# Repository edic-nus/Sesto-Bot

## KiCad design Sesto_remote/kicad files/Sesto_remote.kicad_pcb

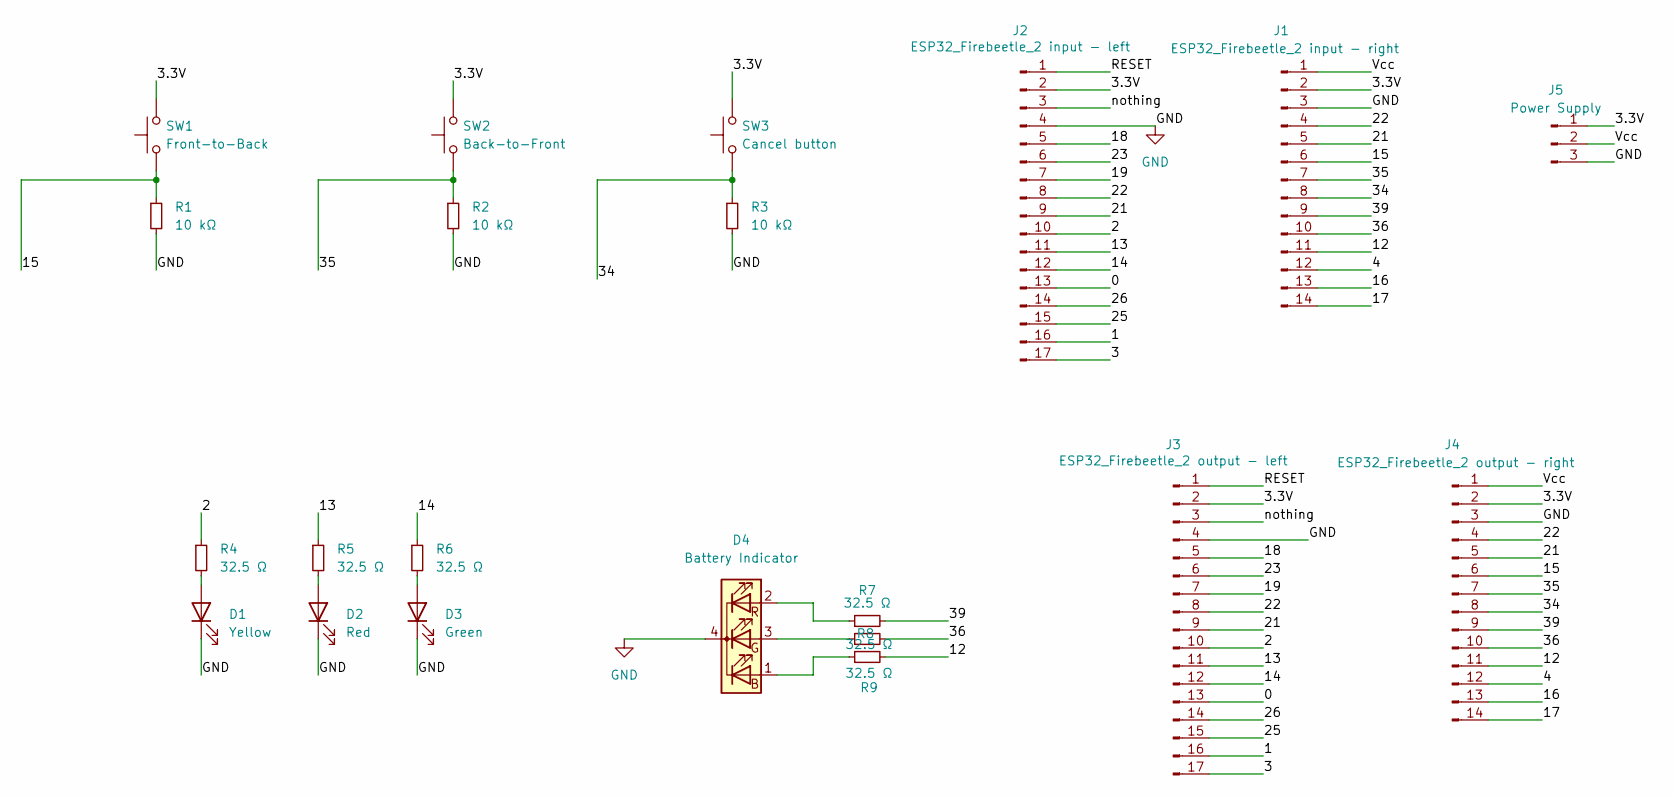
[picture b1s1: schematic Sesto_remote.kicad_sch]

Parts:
D1: Yellow; LED_0603_1608Metric_Pad1.05x0.95mm_HandSolder
D2: Red; LED_0603_1608Metric_Pad1.05x0.95mm_HandSolder
D3: Green; LED_0603_1608Metric_Pad1.05x0.95mm_HandSolder
D4: Battery Indicator; LED_RGB_1210
J1: ESP32_Firebeetle_2 input - right; PinHeader_1x14_P2.54mm_Vertical
J2: ESP32_Firebeetle_2 input - left; PinHeader_1x17_P2.54mm_Vertical
J3: ESP32_Firebeetle_2 output - left; PinSocket_1x17_P2.54mm_Vertical
J4: ESP32_Firebeetle_2 output - right; PinSocket_1x14_P2.54mm_Vertical
J5: Power Supply; Molex_KK-396_A-41792-0003_1x03_P3.96mm_Horizontal
R1, R2, R3: 10 kΩ; R_1210_3225Metric_Pad1.30x2.65mm_HandSolder
R4, R5, R6, R7, R8, R9: 32.5 Ω; R_1210_3225Metric_Pad1.30x2.65mm_HandSolder
SW1: Front-to-Back; SW_PUSH_6mm
SW2: Back-to-Front; SW_PUSH_6mm
SW3: Cancel button; SW_PUSH_6mm

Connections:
/0: J2.13, J3.13
/1: J2.16, J3.16
/2: J2.10, J3.10, R4.1
/3: J2.17, J3.17
/3.3V: J1.2, J2.2, J3.2, J4.2, J5.1, SW1.2, SW2.2, SW3.2
/4: J1.12, J4.12
/12: J1.11, J4.11, R9.2
/13: J2.11, J3.11, R5.1
/14: J2.12, J3.12, R6.1
/15: J1.6, J4.6, R1.1, SW1.1
/16: J1.13, J4.13
/17: J1.14, J4.14
/18: J2.5, J3.5
/19: J2.7, J3.7
/21: J1.5, J2.9, J3.9, J4.5
/22: J1.4, J2.8, J3.8, J4.4
/23: J2.6, J3.6
/25: J2.15, J3.15
/26: J2.14, J3.14
/34: J1.8, J4.8, R3.1, SW3.1
/35: J1.7, J4.7, R2.1, SW2.1
/36: J1.10, J4.10, R8.2
/39: J1.9, J4.9, R7.2
/RESET: J2.1, J3.1
/Vcc: J1.1, J4.1, J5.2
/nothing: J2.3, J3.3
GND: D1.1 (K), D2.1 (K), D3.1 (K), D4.4 (K), J1.3, J2.4, J3.4, J4.3, J5.3, R1.2, R2.2, R3.2
unnamed: D1.2 (A), R4.2
unnamed: D2.2 (A), R5.2
unnamed: D3.2 (A), R6.2
unnamed: D4.1 (BA), R9.1
unnamed: D4.3 (GA), R8.1
unnamed: D4.2 (RA), R7.1

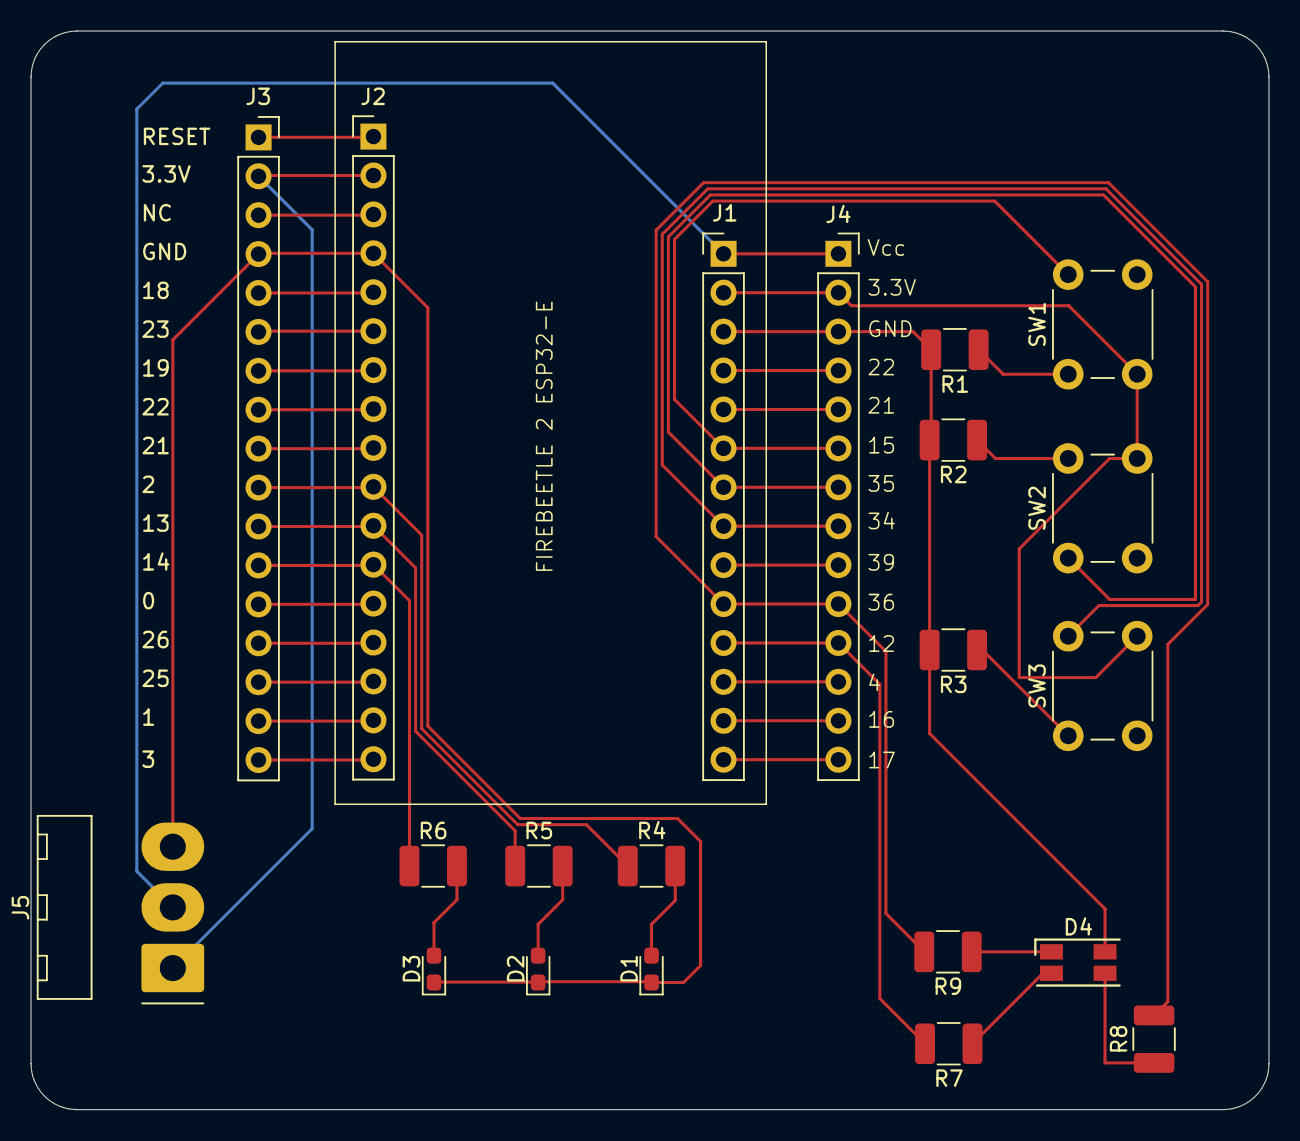
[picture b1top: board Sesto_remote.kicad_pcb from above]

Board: 2 copper layers, 80.8 x 70.4 mm, 21 parts (0 on the bottom side), 33 nets.

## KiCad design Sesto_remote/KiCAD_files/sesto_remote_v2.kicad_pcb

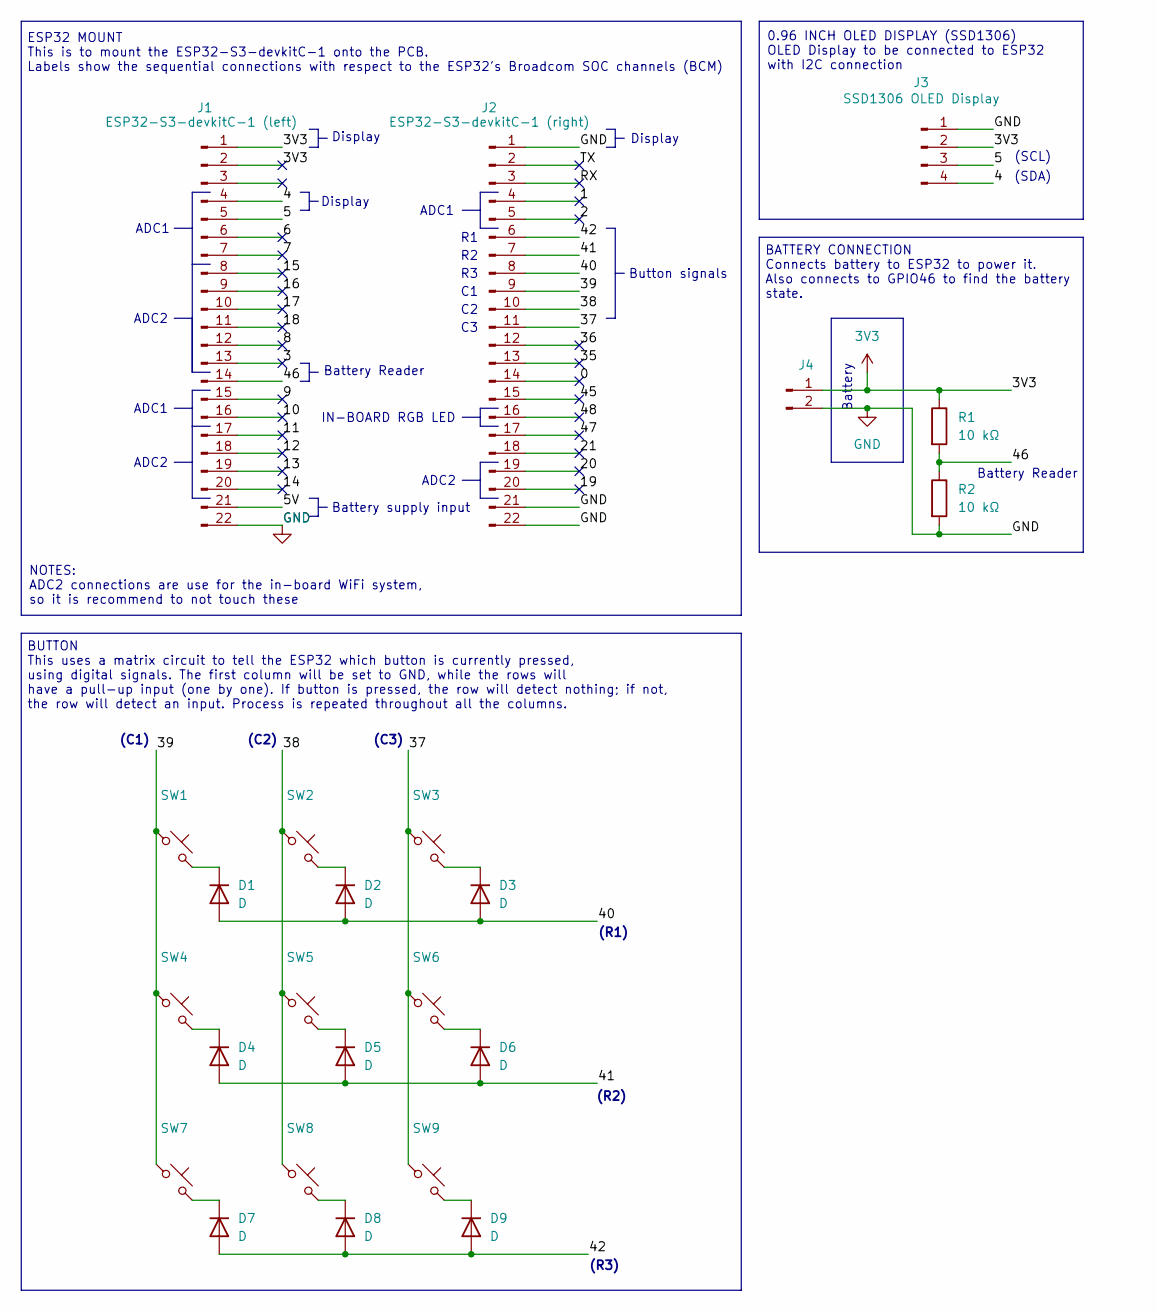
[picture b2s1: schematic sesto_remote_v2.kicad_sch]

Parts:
D1, D2, D3, D4, D5, D6, D7, D8, D9: D; D_0603_1608Metric
J1: ESP32-S3-devkitC-1 (left); PinSocket_1x22_P2.54mm_Vertical
J2: ESP32-S3-devkitC-1 (right); PinSocket_1x22_P2.54mm_Vertical
J3: SSD1306 OLED Display; PinHeader_1x04_P2.54mm_Horizontal
J4: Conn_01x02_Pin; JST_PH_S2B-PH-SM4-TB_1x02-1MP_P2.00mm_Horizontal
R1, R2: 10 kΩ; R_Axial_DIN0204_L3.6mm_D1.6mm_P5.08mm_Horizontal
SW1, SW2, SW3, SW4, SW5, SW6, SW7, SW8, SW9: SW_Push_45deg; SW_Cherry_MX_1.00u_PCB

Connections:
3V3: J1.1, J1.2, J3.2, J4.1, R1.1
/0: J2.14
/1: J2.4
/2: J2.5
/3: J1.13
/4: J1.4, J3.4
/5: J1.5, J3.3
/5V: J1.21
/6: J1.6
/7: J1.7
/8: J1.12
/9: J1.15
/10: J1.16
/11: J1.17
/12: J1.18
/13: J1.19
/14: J1.20
/15: J1.8
/16: J1.9
/17: J1.10
/18: J1.11
/19: J2.20
/20: J2.19
/21: J2.18
/35: J2.13
/36: J2.12
/37: J2.11, SW3.1, SW6.1, SW9.1
/38: J2.10, SW2.1, SW5.1, SW8.1
/39: J2.9, SW1.1, SW4.1, SW7.1
/40: D1.2 (A), D2.2 (A), D3.2 (A), J2.8
/41: D4.2 (A), D5.2 (A), D6.2 (A), J2.7
/42: D7.2 (A), D8.2 (A), D9.2 (A), J2.6
/45: J2.15
/46: J1.14, R1.2, R2.1
/47: J2.17
/48: J2.16
/RX: J2.3
/TX: J2.2
GND: J1.22, J2.1, J2.21, J2.22, J3.1, J4.2, R2.2
unnamed: D1.1 (K), SW1.2
unnamed: D2.1 (K), SW2.2
unnamed: D3.1 (K), SW3.2
unnamed: D4.1 (K), SW4.2
unnamed: D5.1 (K), SW5.2
unnamed: D6.1 (K), SW6.2
unnamed: D7.1 (K), SW7.2
unnamed: D8.1 (K), SW8.2
unnamed: D9.1 (K), SW9.2

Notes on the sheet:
(C2)
ADC2
Button signals
Battery Reader
Battery
Display
BUTTON This uses a matrix circuit to tell the ESP32 which button is currently pressed, using digital signals. The first column will be set to GND, while the rows will have a pull-up input (one by one). If button is pressed, the row will detect nothing; if not, the row will detect an input. Process 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
(R1)
NOTES: ADC2 connections are use for the in-board WiFi system, so it is recommend to not touch these
Battery Reader
Battery supply input
(R3)
ESP32 MOUNT This is to mount the ESP32-S3-devkitC-1 onto the PCB. Labels show the sequential connections with respect to the ESP32's Broadcom SOC channels (BCM)
(R2)
ADC1
(C1)
IN-BOARD RGB LED
(C3)
0.96 INCH OLED DISPLAY (SSD1306) OLED Display to be connected to ESP32 with I2C connection
BATTERY CONNECTION Connects battery to ESP32 to power it. Also connects to GPIO46 to find the battery state.
(SDA)
(SCL)

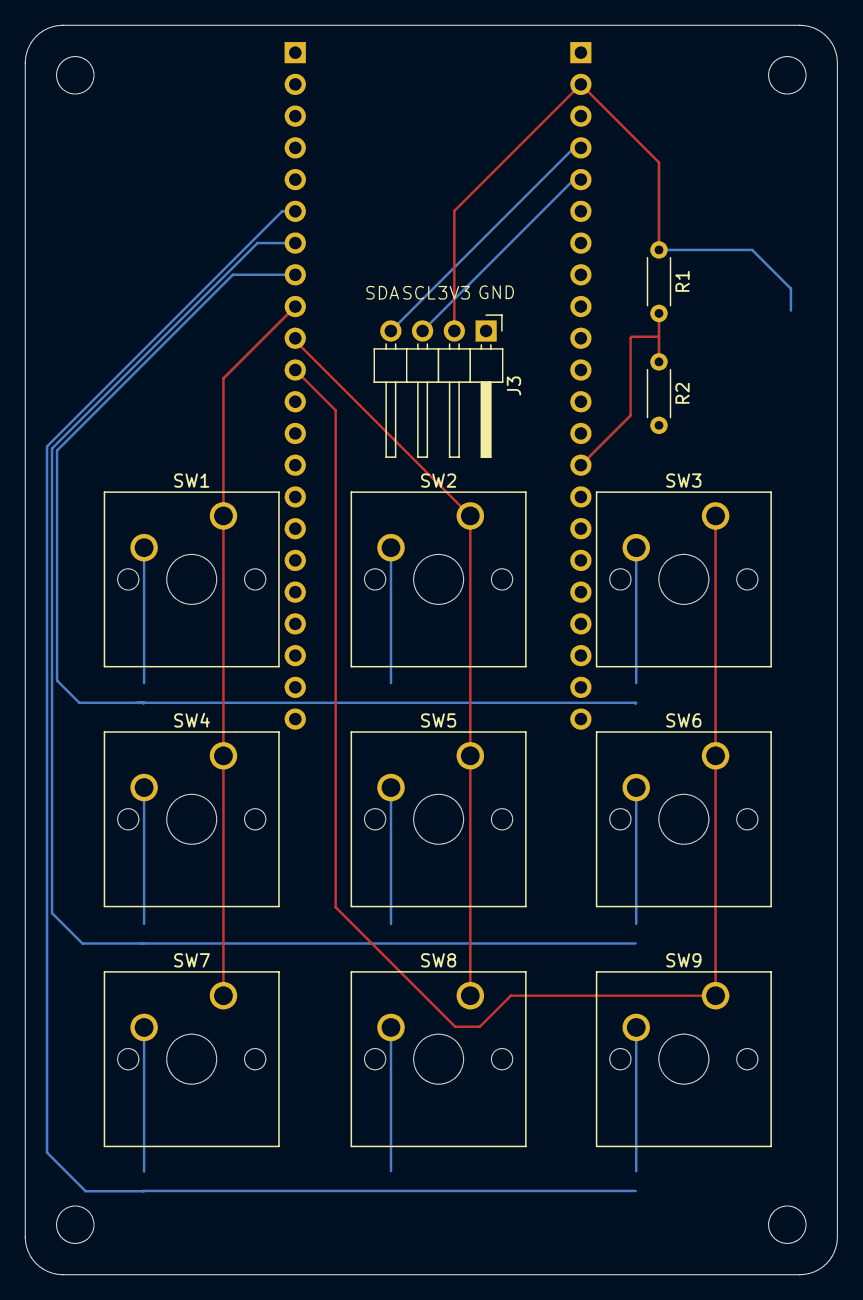
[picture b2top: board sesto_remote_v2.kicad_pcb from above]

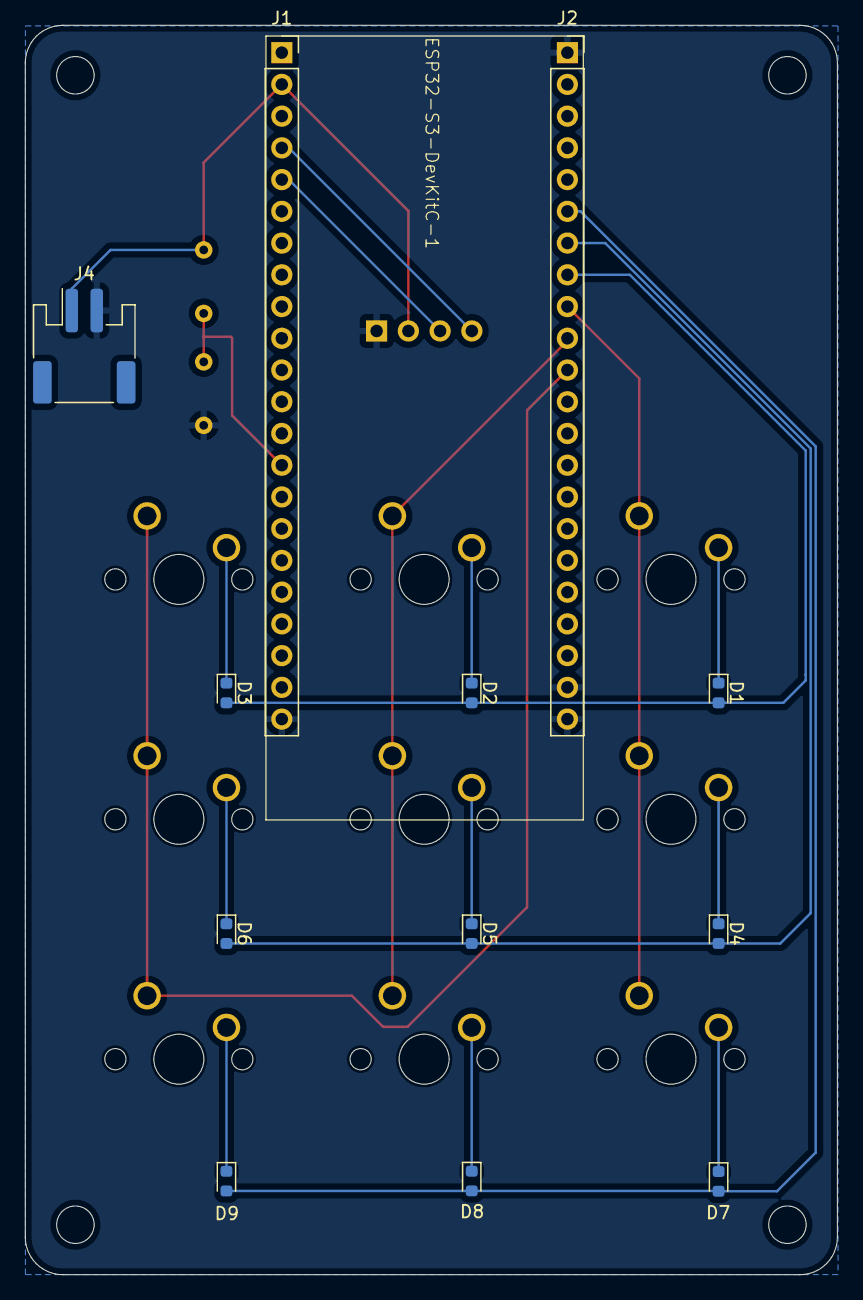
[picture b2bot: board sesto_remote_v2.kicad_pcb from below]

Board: 2 copper layers, 65.0 x 100.0 mm, 24 parts (12 on the bottom side), 20 nets.

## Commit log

2024-06-28 Create ESP32_relay_door.ino
    ESP32 relay door opener
2024-07-07 added files for sesto remote pcb design review
2024-07-17 Added remote control pcb v2
2024-07-17 Added schematic file for easier access
2024-07-17 Create battery_checker.ino
    just adding it here in case I lost it inside my pc for whatever reason
2024-07-17 Rename Sesto_remote/mechanical_switch.ino to Sesto_remote/Codes/mechanical_switch.ino
    Move to Codes directory
2024-07-17 Rename Sesto_remote/Sesto_remote_v2_schematics.pdf to Sesto_remote/KiCAD_files/Sesto_remote_v2_schematics.pdf
    Moving files
2024-07-17 Rename Sesto_remote/sesto_remote_v2.kicad_pcb to Sesto_remote/KiCAD_files/sesto_remote_v2.kicad_pcb
2024-07-17 Rename Sesto_remote/sesto_remote_v2.kicad_prl to Sesto_remote/KiCAD_files/sesto_remote_v2.kicad_prl
2024-07-17 Rename Sesto_remote/sesto_remote_v2.kicad_pro to Sesto_remote/KiCAD_files/sesto_remote_v2.kicad_pro
2024-07-17 Rename Sesto_remote/sesto_remote_v2.kicad_sch to Sesto_remote/KiCAD_files/sesto_remote_v2.kicad_sch
2024-07-17 Rename Sesto_remote/~sesto_remote_v2.kicad_pcb.lck to Sesto_remote/KiCAD_files/~sesto_remote_v2.kicad_pcb.lck
2024-07-24 Create master.ino
    @roystonshieh the uploaded code here is to scroll through the different functions of the remote control horizontally, which is displayed on the SSD1306 0.96 inch display. The code here is about three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
    For the PCB, I have already purchased it. It will arrive in about 2 weeks from now, which although not ideal, I do not mind overworking for a few more weeks to finish this project.
    The PCB total cost is 41.56 USD. If needed, I will send the BoM here later.
    For the documentation, me and @cyanhere are currently writing it together, should fin
2024-07-27 Update master.ino
    Added the request functionalities into the code, and updated the UI, where when selecting "tinkering corner" or "sandbox", there will be a top screen scrolling down, showing the user the options to e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
    When choosing the "battery" option, there will only have the battery level of the remote control. For now, I am unable to check for battery levels yet, because I don't have a battery on hand at the m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
    When choosing the "open cabinet" option, the remote should open the cabinet mounted on top of the SESTO robot. Further testing is required next week.
    Functionalities of the code may be buggy, needs some testing with the SE
2024-08-14 version 1 code
2024-08-14 Used to localize the sestobot through constant pinging of its online offline status. Will deem the sesto to be back at home when it is offline.
2024-08-14 First version of task queuing via API
    Ensure that the bearer code is obtained from the sesto through a post request for authentication
2024-08-14 Base code for the door receiver, commented out test code.
2024-08-16 Minor update master.ino (tested with PCB)
    - Changed the button numbers around such that it matches with the documentation descriptions
2024-08-28 Update master.ino
    Updated code such that when closing the remote control screen, the esp resets itself so that the code can be rerun from the very start. ( at setup() )
